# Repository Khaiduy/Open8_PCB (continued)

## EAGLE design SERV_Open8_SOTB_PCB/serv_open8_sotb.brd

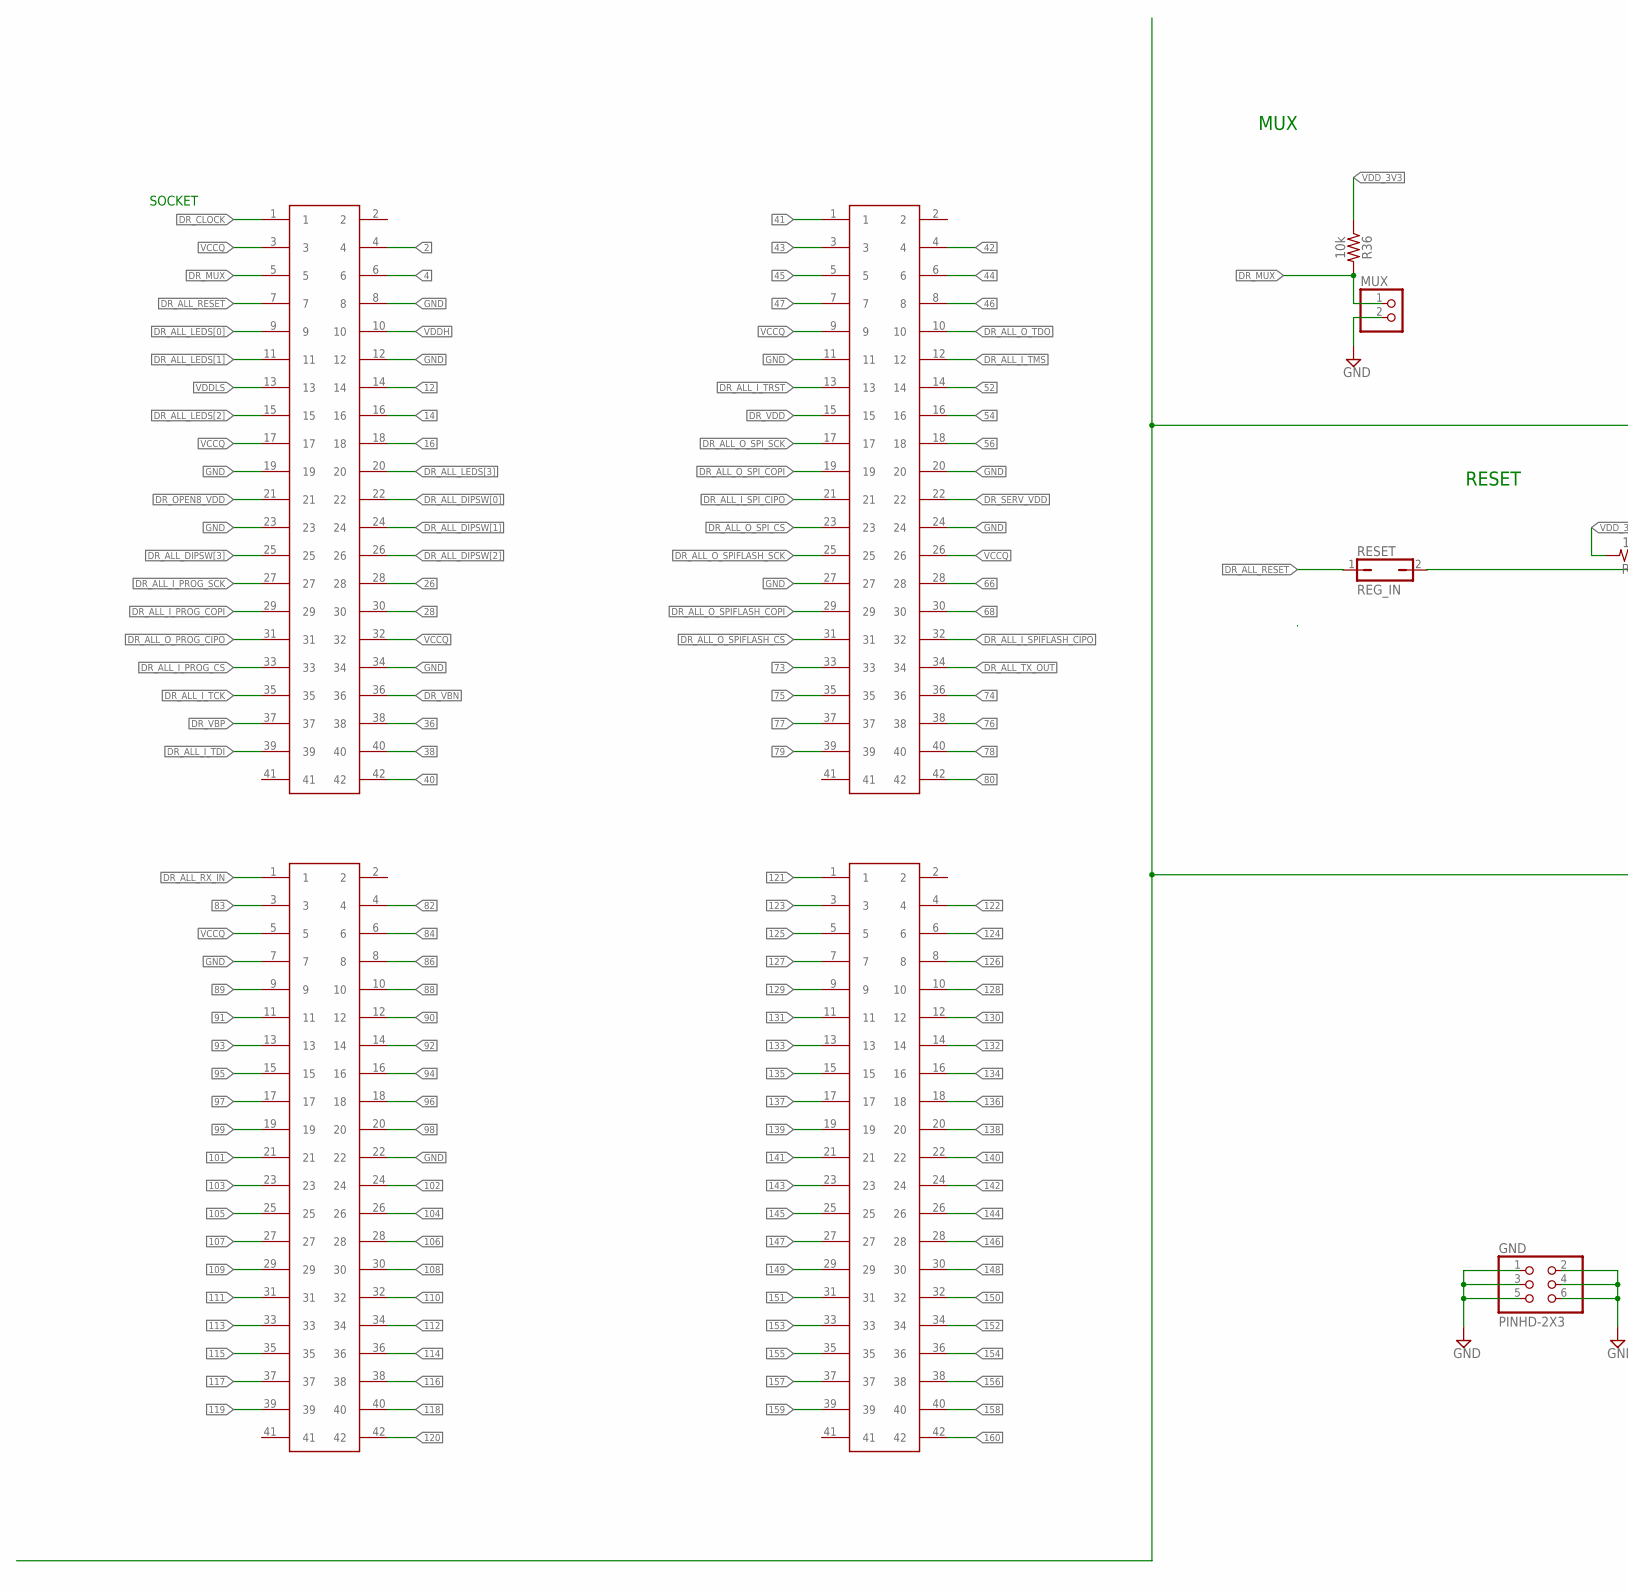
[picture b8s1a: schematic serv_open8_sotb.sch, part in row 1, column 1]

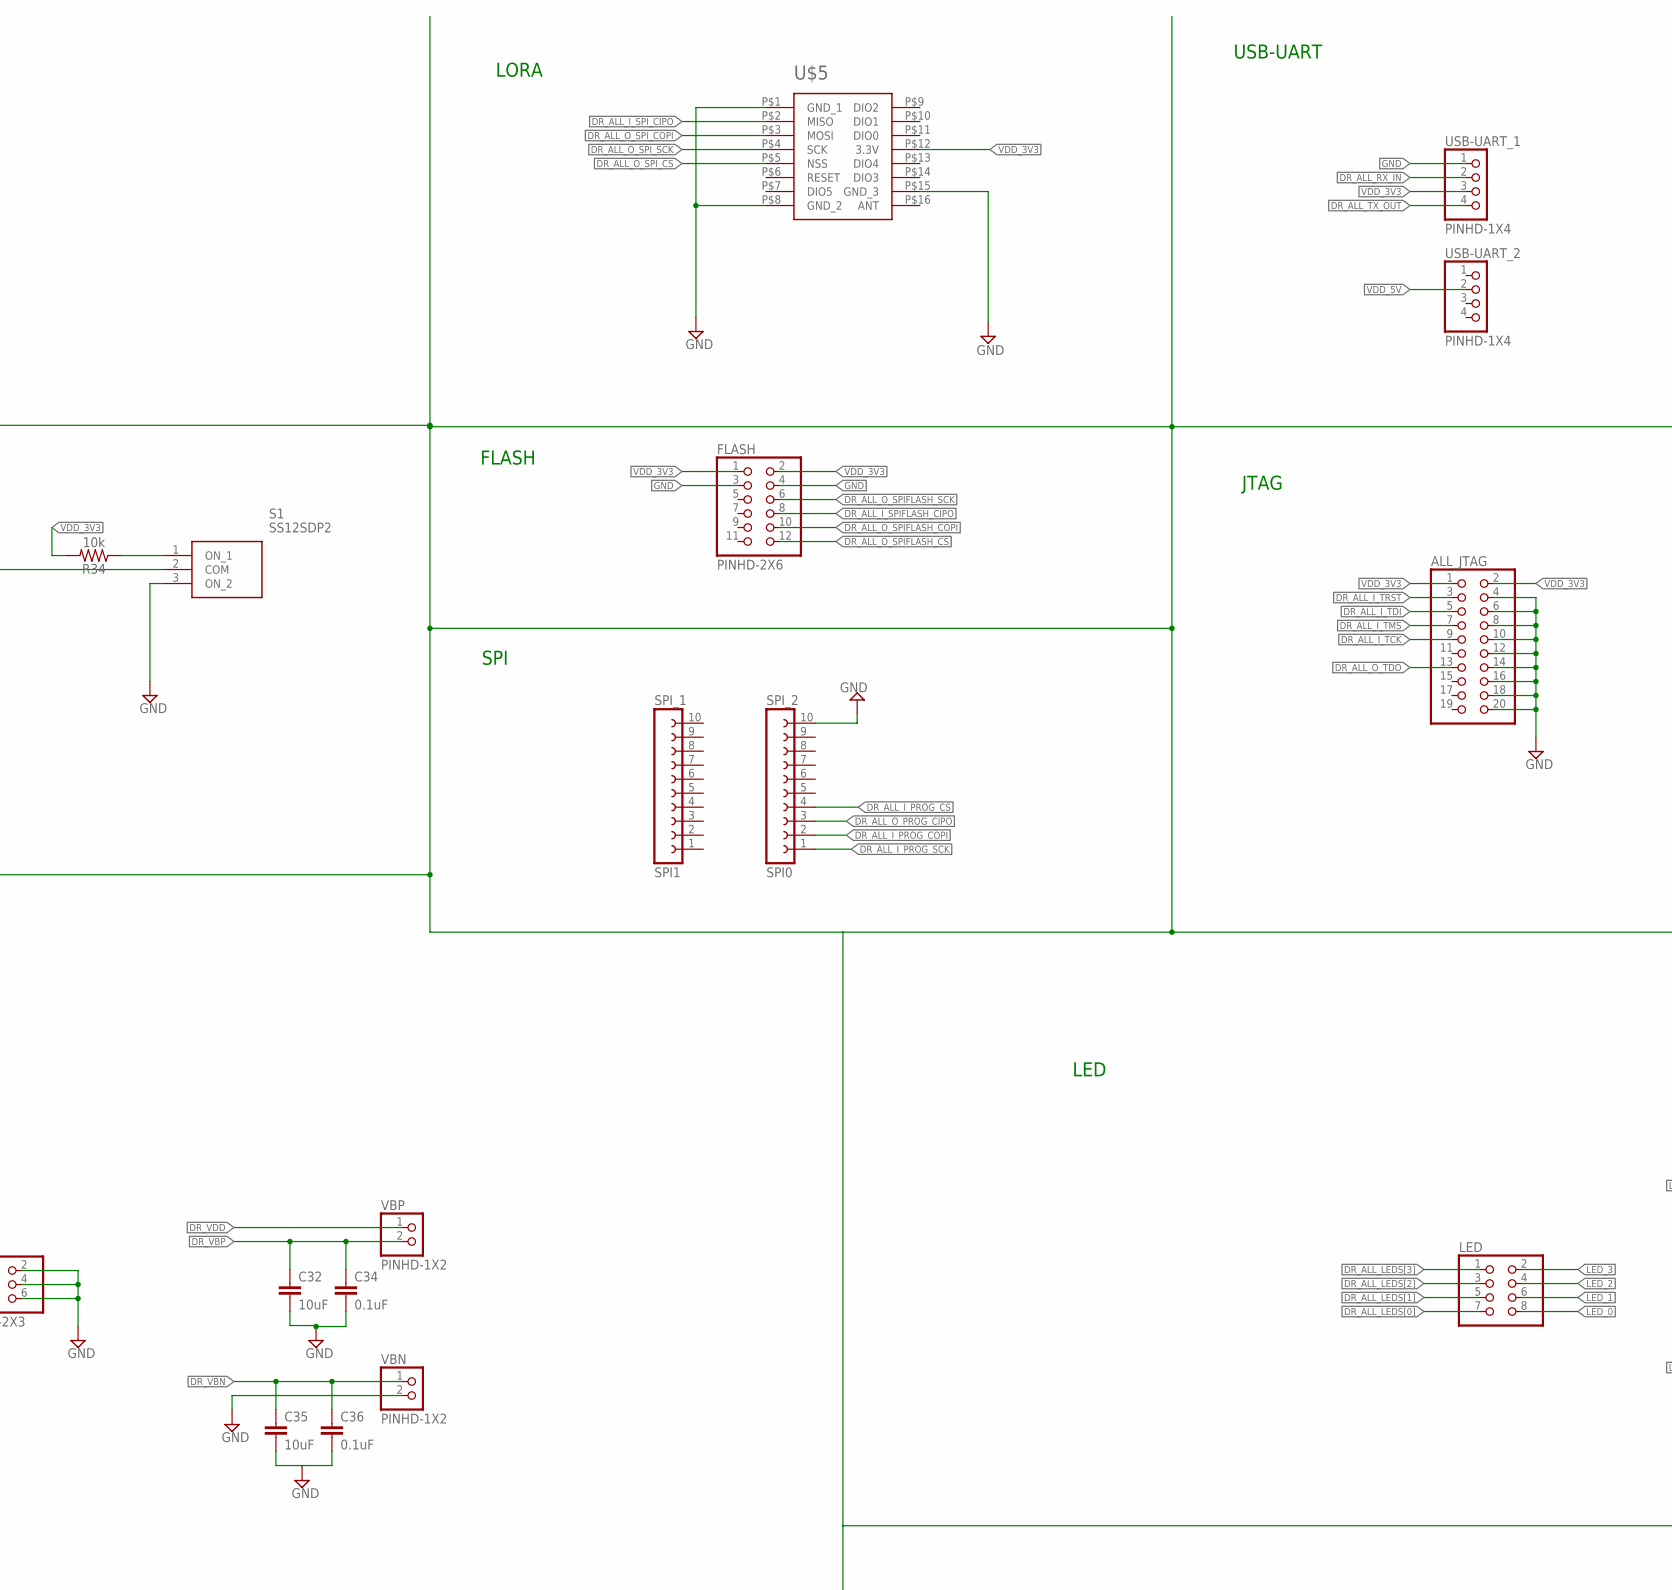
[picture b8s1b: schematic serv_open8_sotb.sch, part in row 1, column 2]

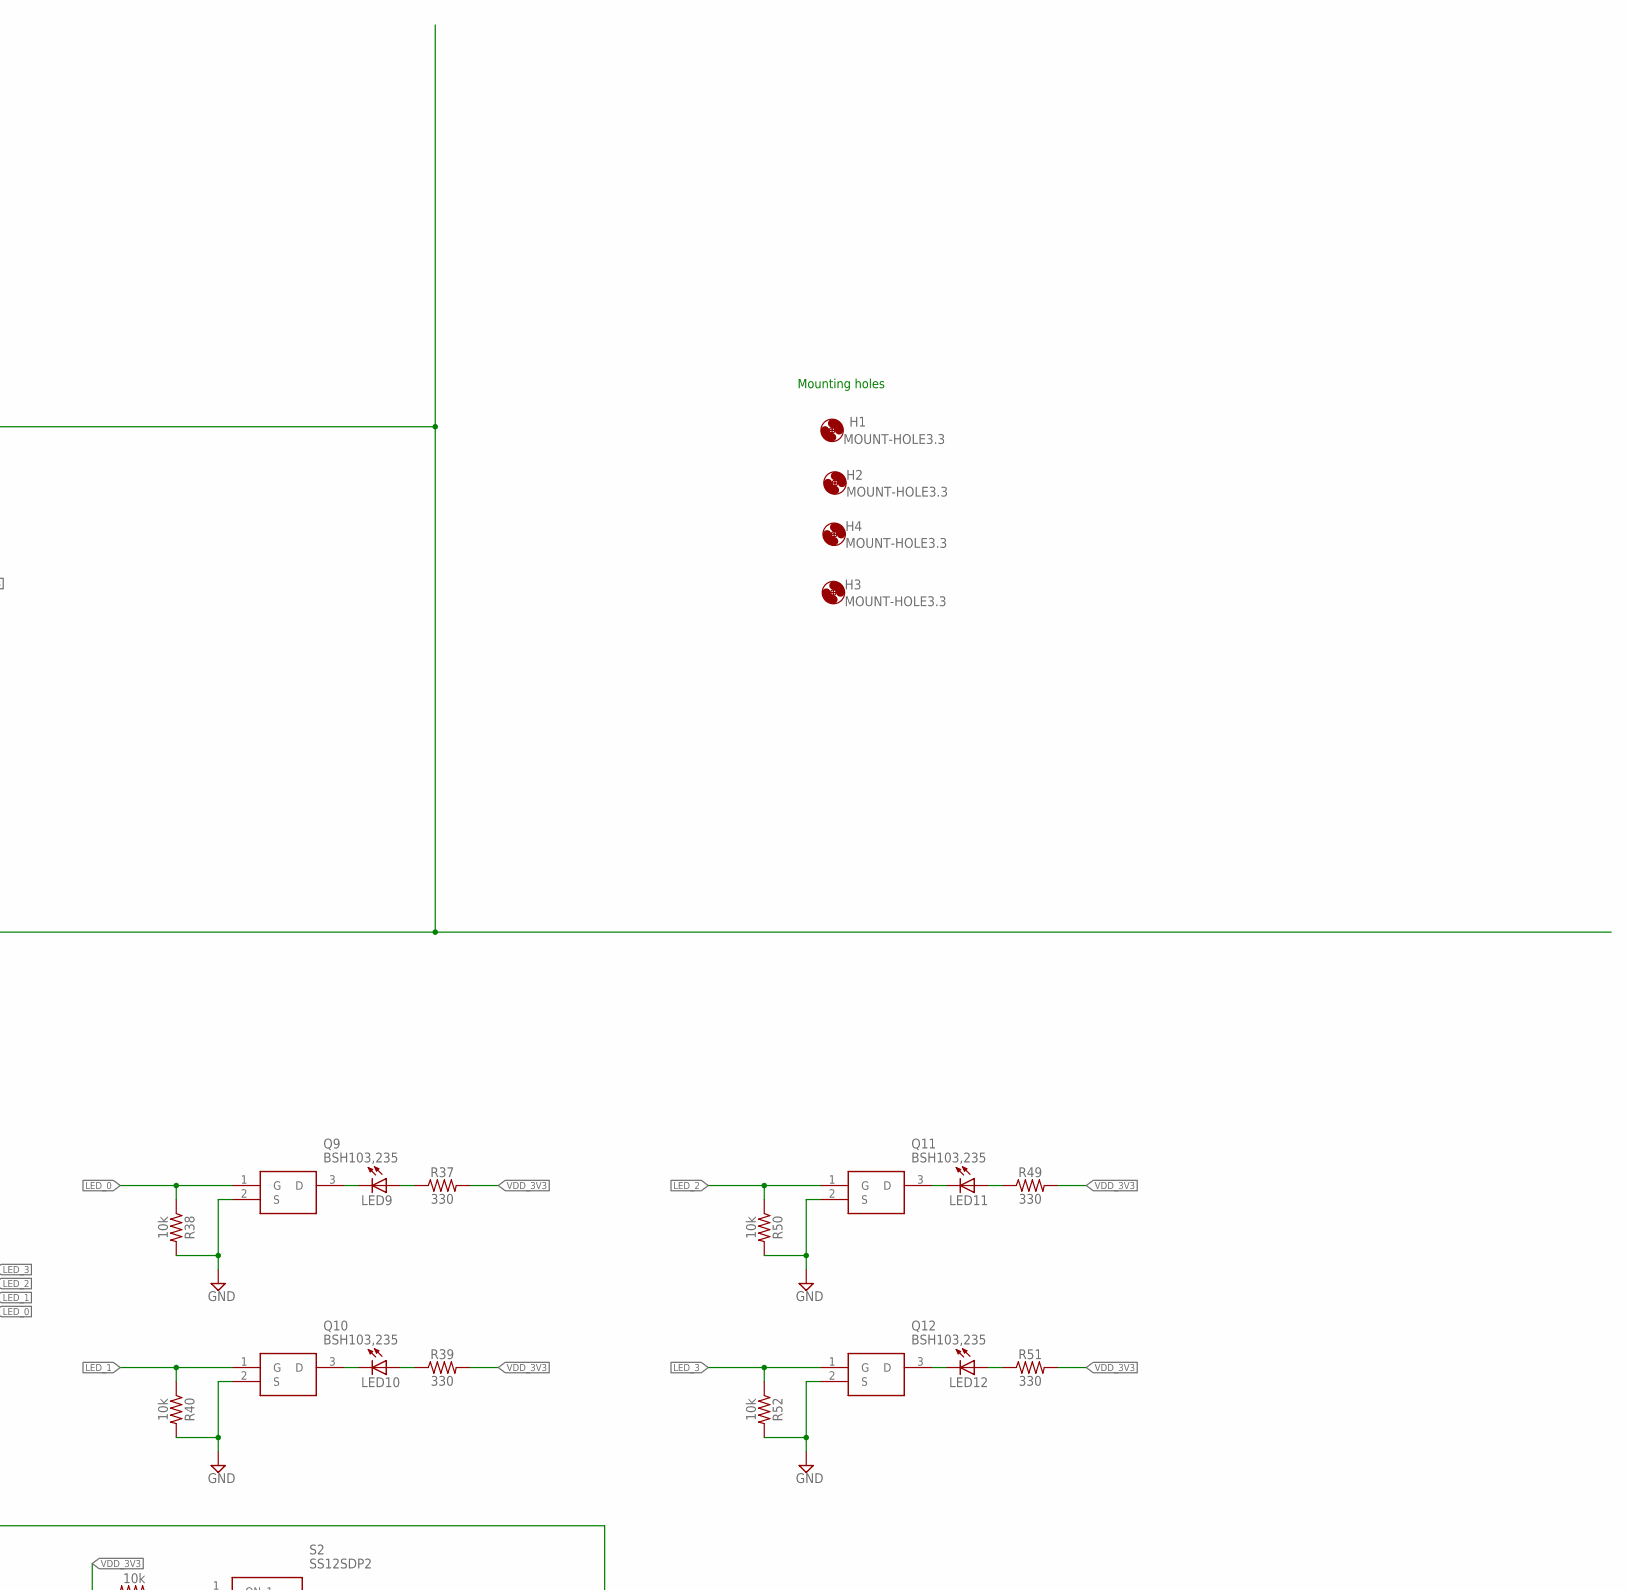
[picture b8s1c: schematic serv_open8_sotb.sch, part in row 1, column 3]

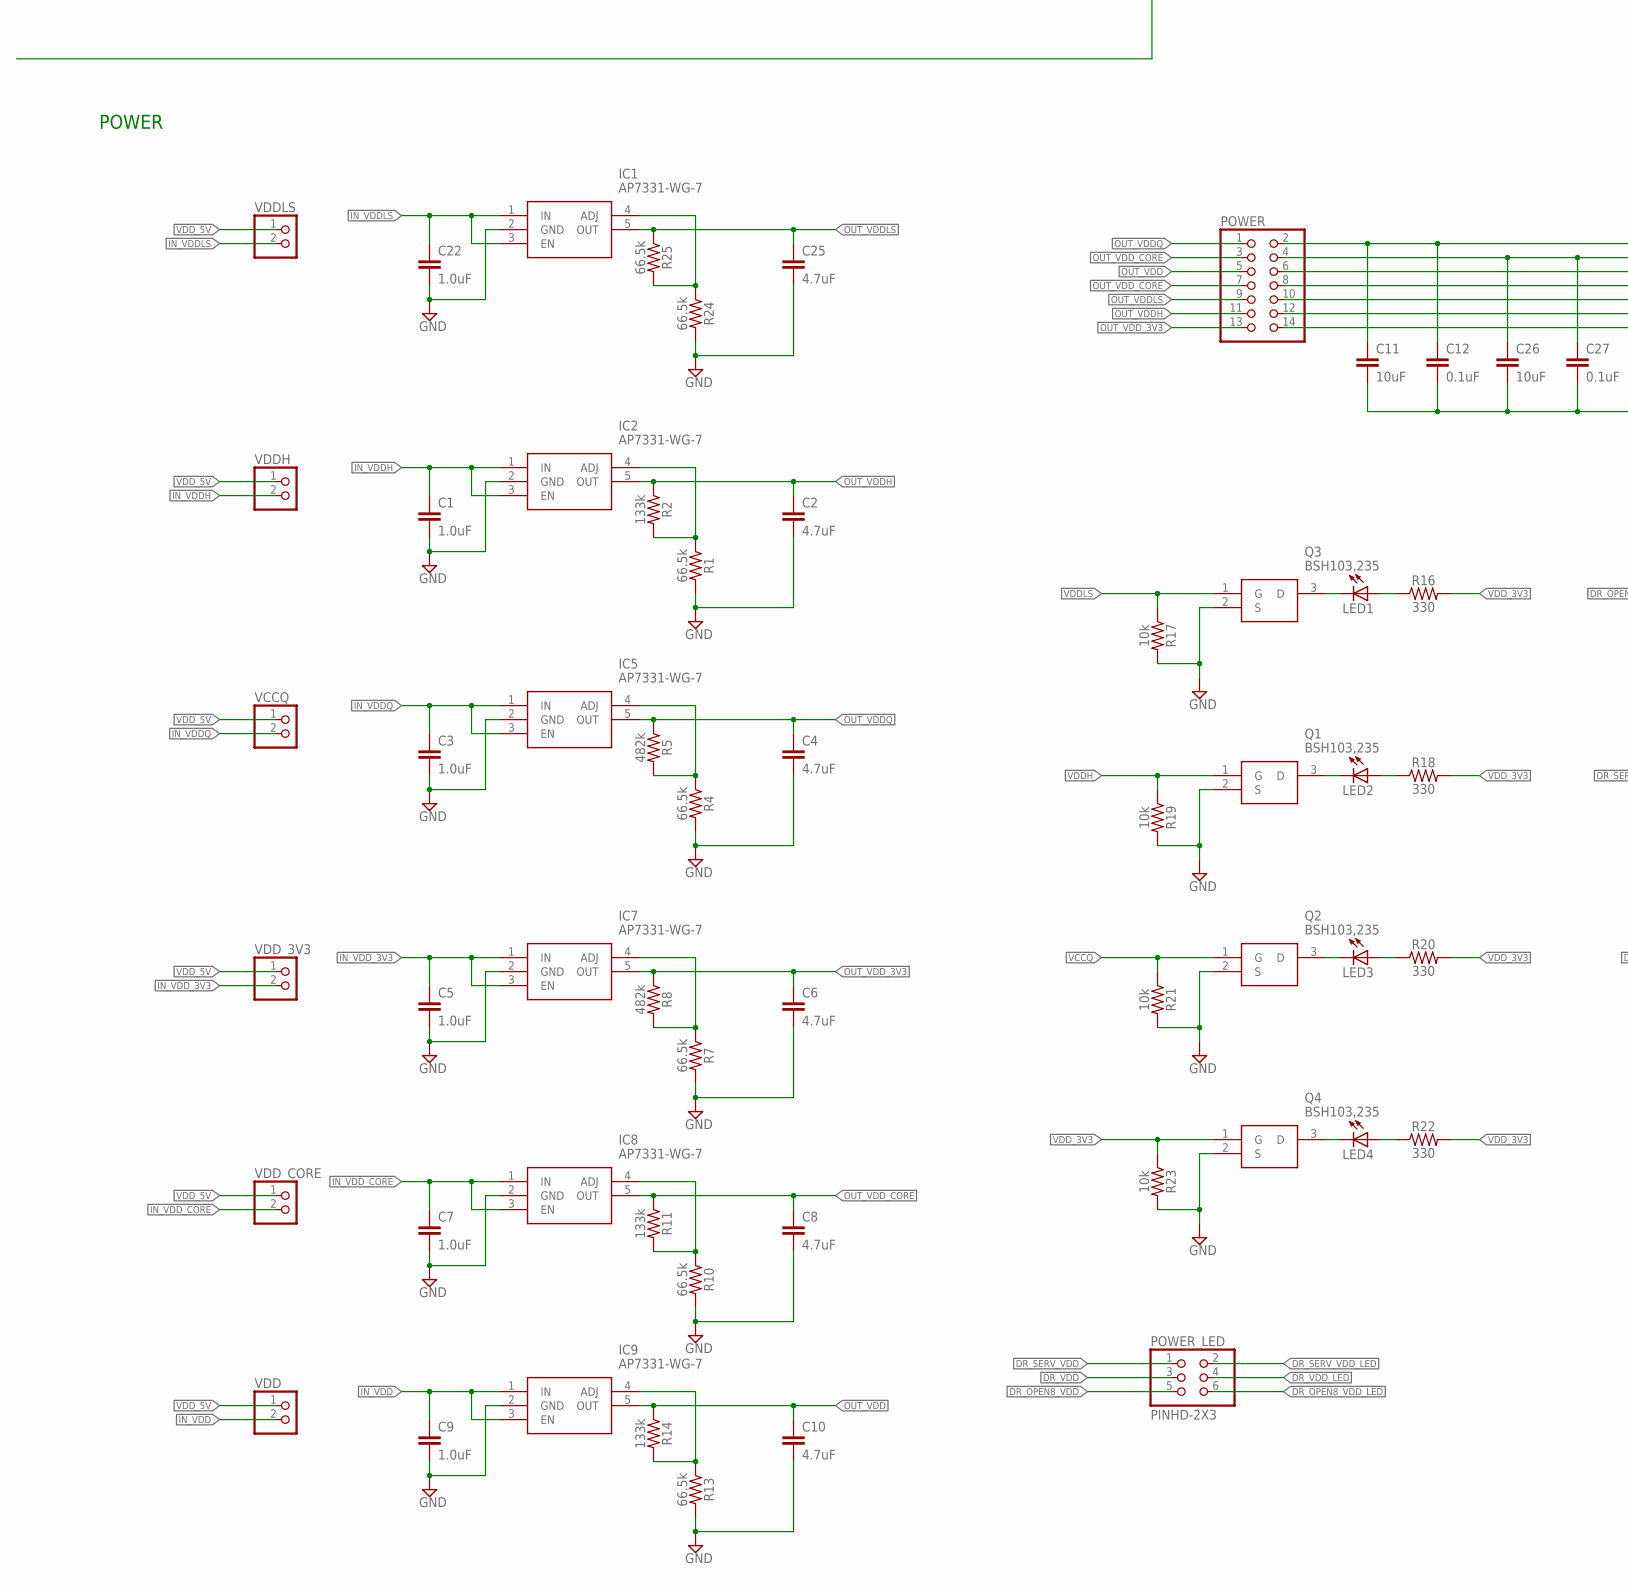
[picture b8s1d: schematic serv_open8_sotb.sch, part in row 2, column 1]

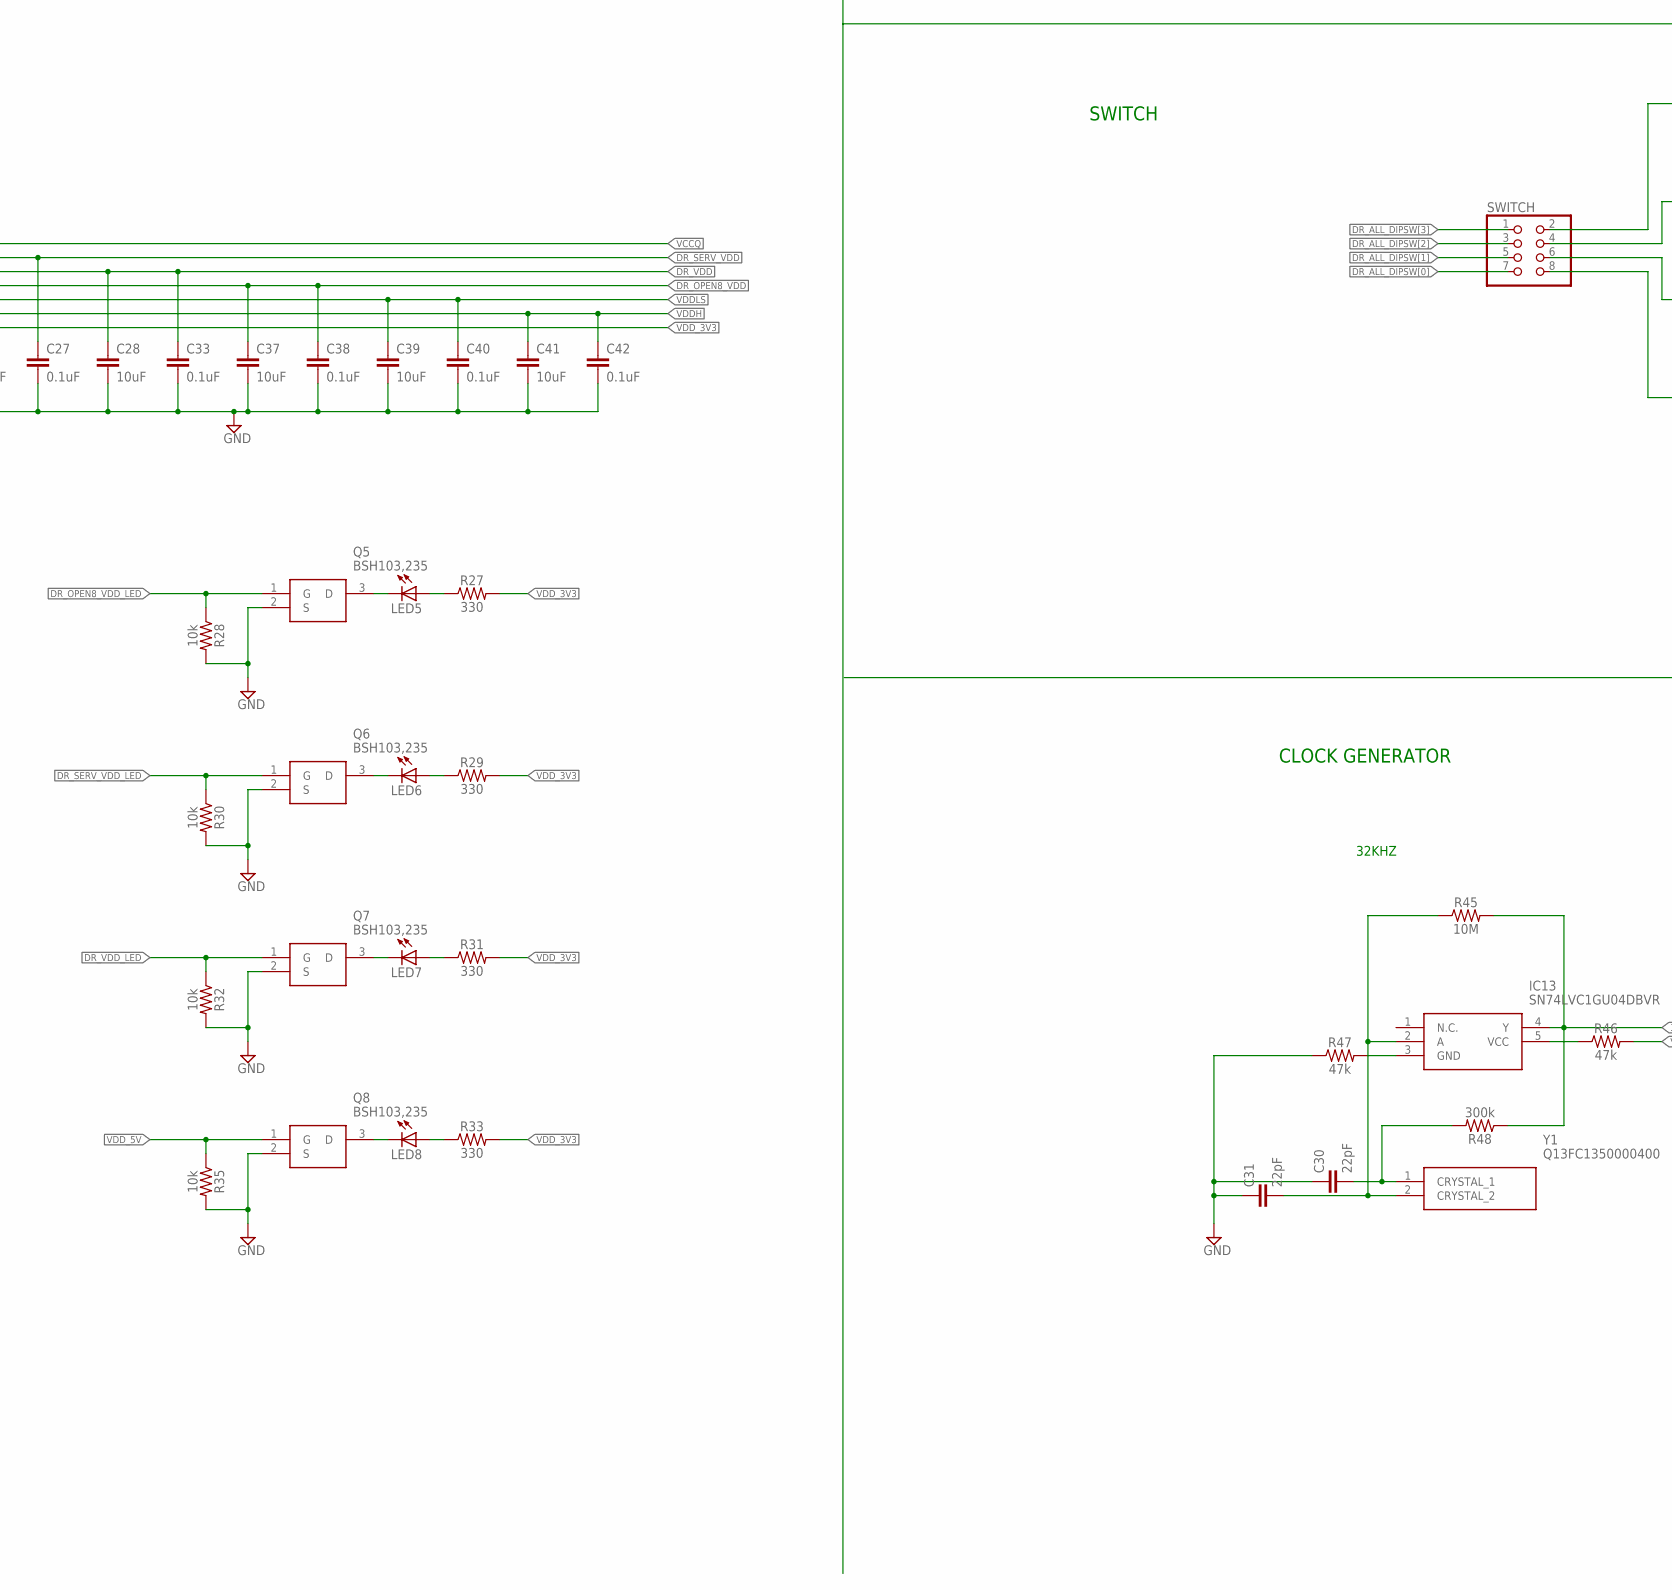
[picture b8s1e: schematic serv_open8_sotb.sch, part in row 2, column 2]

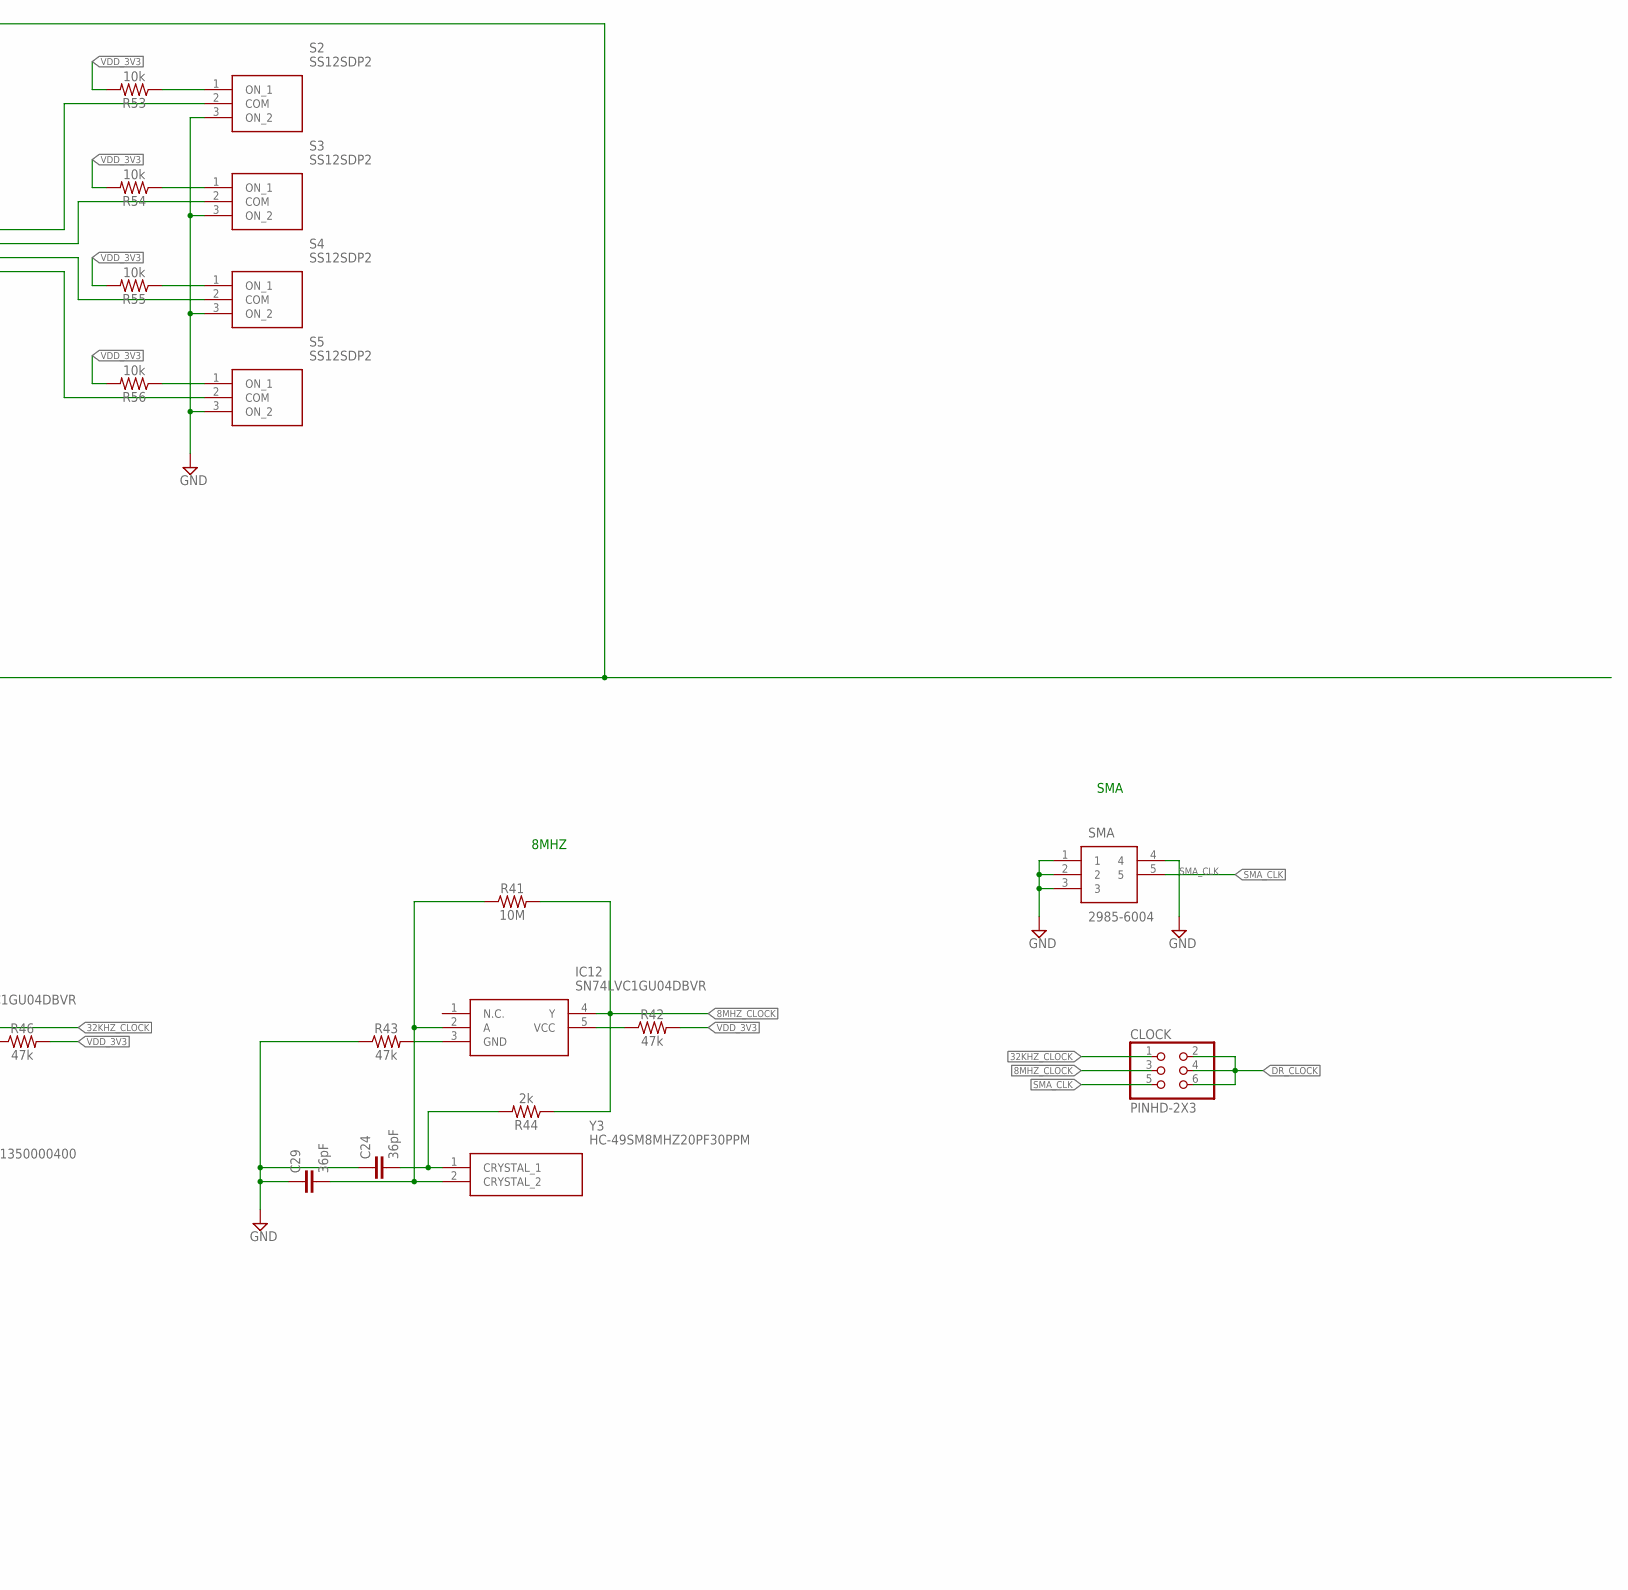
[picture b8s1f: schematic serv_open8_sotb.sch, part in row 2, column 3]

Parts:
ALL_JTAG: PINHD-2X10; 2X10
C1, C3, C5, C7, C9, C22: 1.0uF; 0805
C2, C4, C6, C8, C10, C25: 4.7uF; 0805
C11, C26, C28, C32, C35, C37, C39, C41: 10uF; 0805
C12, C27, C33, C34, C36, C38, C40, C42: 0.1uF; 0805
C24, C29: 36pF; 0805
C30, C31: 22pF; 0805
CLOCK: PINHD-2X3; 2X03
FLASH: PINHD-2X6; 2X06
GND: PINHD-2X3; 2X03
H1, H2, H3, H4: MOUNT-HOLE3.3; 3,3
IC1, IC2, IC5, IC7, IC8, IC9: AP7331-WG-7; SOT95P285X145-5N
IC12, IC13: SN74LVC1GU04DBVR; SOT95P280X145-5N
LED: PINHD-2X4; 2X04
LED1, LED2, LED3, LED4, LED5, LED6, LED7, LED8, LED9, LED10, LED11, LED12: LEDCHIP-LED0805; CHIP-LED0805
MUX: PINHD-1X2; 1X02
POWER: PINHD-2X7; 2X07
POWER_LED: PINHD-2X3; 2X03
Q1, Q2, Q3, Q4, Q5, Q6, Q7, Q8, Q9, Q10, Q11, Q12: BSH103,235; SOT95P230X110-3N
R1, R4, R7, R10, R13, R24, R25: 66.5k; 0805
R2, R11, R14: 133k; 0805
R5, R8: 482k; 0805
R16, R18, R20, R22, R27, R29, R31, R33, R37, R39, R49, R51: 330; 0805
R17, R19, R21, R23, R28, R30, R32, R34, R35, R36, R38, R40, R50, R52, R53, R54, R55, R56: 10k; 0805
R41, R45: 10M; 0805
R42, R43, R46, R47: 47k; 0805
R44: 2k; 0805
R48: 300k; 0805
RESET: REG_IN; JP1
S1, S2, S3, S4, S5: SS12SDP2
SMA: 2985-6004; 29856004
SPI_1: SPI1; FE10
SPI_2: SPI0; FE10
SWITCH: PINHD-2X4; 2X04
U$1, U$2, U$3, U$4: 2X41_HEADER
U$5: RFM95W-915S2
USB-UART_1, USB-UART_2: PINHD-1X4; 1X04
VBN: PINHD-1X2; 1X02
VBP: PINHD-1X2; 1X02
VCCQ: PINHD-1X2; 1X02
VDD: PINHD-1X2; 1X02
VDDH: PINHD-1X2; 1X02
VDDLS: PINHD-1X2; 1X02
VDD_3V3: PINHD-1X2; 1X02
VDD_CORE: PINHD-1X2; 1X02
Y1: Q13FC1350000400
Y3: HC-49SM8MHZ20PF30PPM; HC49SM8MHZ20PF30PPM

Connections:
2: U$1.4
4: U$1.6
8MHZ_CLOCK: CLOCK.3, IC12.4 (Y), R41.2, R44.1
12: U$1.14
14: U$1.16
16: U$1.18
26: U$1.28
28: U$1.30
32KHZ_CLOCK: CLOCK.1, IC13.4 (Y), R45.2, R48.1
36: U$1.38
38: U$1.40
40: U$1.42
41: U$2.1
42: U$2.4
43: U$2.3
44: U$2.6
45: U$2.5
46: U$2.8
47: U$2.7
52: U$2.14
54: U$2.16
56: U$2.18
66: U$2.28
68: U$2.30
73: U$2.33
74: U$2.36
75: U$2.35
76: U$2.38
77: U$2.37
78: U$2.40
79: U$2.39
80: U$2.42
82: U$3.4
83: U$3.3
84: U$3.6
86: U$3.8
88: U$3.10
89: U$3.9
90: U$3.12
91: U$3.11
92: U$3.14
93: U$3.13
94: U$3.16
95: U$3.15
96: U$3.18
97: U$3.17
98: U$3.20
99: U$3.19
101: U$3.21
102: U$3.24
103: U$3.23
104: U$3.26
105: U$3.25
106: U$3.28
107: U$3.27
108: U$3.30
109: U$3.29
110: U$3.32
111: U$3.31
112: U$3.34
113: U$3.33
114: U$3.36
115: U$3.35
116: U$3.38
117: U$3.37
118: U$3.40
119: U$3.39
120: U$3.42
121: U$4.1
122: U$4.4
123: U$4.3
124: U$4.6
125: U$4.5
126: U$4.8
127: U$4.7
128: U$4.10
129: U$4.9
130: U$4.12
131: U$4.11
132: U$4.14
133: U$4.13
134: U$4.16
135: U$4.15
136: U$4.18
137: U$4.17
138: U$4.20
139: U$4.19
140: U$4.22
141: U$4.21
142: U$4.24
143: U$4.23
144: U$4.26
145: U$4.25
146: U$4.28
147: U$4.27
148: U$4.30
149: U$4.29
150: U$4.32
151: U$4.31
152: U$4.34
153: U$4.33
154: U$4.36
155: U$4.35
156: U$4.38
157: U$4.37
158: U$4.40
159: U$4.39
160: U$4.42
DR_ALL_DIPSW[0]: SWITCH.7, U$1.22
DR_ALL_DIPSW[1]: SWITCH.5, U$1.24
DR_ALL_DIPSW[2]: SWITCH.3, U$1.26
DR_ALL_DIPSW[3]: SWITCH.1, U$1.25
DR_ALL_I_PROG_COPI: SPI_2.2, U$1.29
DR_ALL_I_PROG_CS: SPI_2.4, U$1.33
DR_ALL_I_PROG_SCK: SPI_2.1, U$1.27
DR_ALL_I_SPIFLASH_CIPO: FLASH.8, U$2.32
DR_ALL_I_SPI_CIPO: U$2.21, U$5.P$2 (MISO)
DR_ALL_I_TCK: ALL_JTAG.9, U$1.35
DR_ALL_I_TDI: ALL_JTAG.5, U$1.39
DR_ALL_I_TMS: ALL_JTAG.7, U$2.12
DR_ALL_I_TRST: ALL_JTAG.3, U$2.13
DR_ALL_LEDS[0]: LED.7, U$1.9
DR_ALL_LEDS[1]: LED.5, U$1.11
DR_ALL_LEDS[2]: LED.3, U$1.15
DR_ALL_LEDS[3]: LED.1, U$1.20
DR_ALL_O_PROG_CIPO: SPI_2.3, U$1.31
DR_ALL_O_SPIFLASH_COPI: FLASH.10, U$2.29
DR_ALL_O_SPIFLASH_CS: FLASH.12, U$2.31
DR_ALL_O_SPIFLASH_SCK: FLASH.6, U$2.25
DR_ALL_O_SPI_COPI: U$2.19, U$5.P$3 (MOSI)
DR_ALL_O_SPI_CS: U$2.23, U$5.P$5 (NSS)
DR_ALL_O_SPI_SCK: U$2.17, U$5.P$4 (SCK)
DR_ALL_O_TDO: ALL_JTAG.13, U$2.10
DR_ALL_RESET: RESET.1, U$1.7
DR_ALL_RX_IN: U$3.1, USB-UART_1.2
DR_ALL_TX_OUT: U$2.34, USB-UART_1.4
DR_CLOCK: CLOCK.2, CLOCK.4, CLOCK.6, U$1.1
DR_MUX: MUX.1, R36.2, U$1.5
DR_OPEN8_VDD: C37.1, C38.1, POWER.8, POWER_LED.5, U$1.21
DR_OPEN8_VDD_LED: POWER_LED.6, Q5.1 (G), R28.1
DR_SERV_VDD: C26.1, C27.1, POWER.4, POWER_LED.1, U$2.22
DR_SERV_VDD_LED: POWER_LED.2, Q6.1 (G), R30.1
DR_VBN: C35.1, C36.1, U$1.36, VBN.1
DR_VBP: C32.1, C34.1, U$1.37, VBP.2
DR_VDD: C28.1, C33.1, POWER.6, POWER_LED.3, U$2.15, VBP.1
DR_VDD_LED: POWER_LED.4, Q7.1 (G), R32.1
GND: ALL_JTAG.4, ALL_JTAG.6, ALL_JTAG.8, ALL_JTAG.10, ALL_JTAG.12, ALL_JTAG.14, ALL_JTAG.16, ALL_JTAG.18, ALL_JTAG.20, C1.2, C2.2, C3.2, C4.2, C5.2, C6.2, C7.2, C8.2, C9.2, C10.2, C11.2, C12.2, C22.2, C24.1, C25.2, C26.2, C27.2, C28.2, C29.1, C30.1, C31.1, C32.2, C33.2, C34.2, C35.2, C36.2, C37.2, C38.2, C39.2, C40.2, C41.2, C42.2, FLASH.3, FLASH.4, GND.1, GND.2, GND.3, GND.4, GND.5, GND.6, IC1.2 (GND), IC2.2 (GND), IC5.2 (GND), IC7.2 (GND), IC8.2 (GND), IC9.2 (GND), MUX.2, Q1.2 (S), Q2.2 (S), Q3.2 (S), Q4.2 (S), Q5.2 (S), Q6.2 (S), Q7.2 (S), Q8.2 (S), Q9.2 (S), Q10.2 (S), Q11.2 (S), Q12.2 (S), R1.2, R4.2, R7.2, R10.2, R13.2, R17.2, R19.2, R21.2, R23.2, R24.2, R28.2, R30.2, R32.2, R35.2, R38.2, R40.2, R43.1, R47.1, R50.2, R52.2, S1.3 (ON_2), S2.3 (ON_2), S3.3 (ON_2), S4.3 (ON_2), S5.3 (ON_2), SMA.1, SMA.2, SMA.3, SMA.4, SPI_2.10, U$1.8, U$1.12, U$1.19, U$1.23, U$1.34, U$2.11, U$2.20, U$2.24, U$2.27, U$3.7, U$3.22, U$5.P$1 (GND_1), U$5.P$8 (GND_2), U$5.P$15 (GND_3), USB-UART_1.1, VBN.2
IN_VDD: C9.1, IC9.1 (IN), IC9.3 (EN), VDD.2
IN_VDDH: C1.1, IC2.1 (IN), IC2.3 (EN), VDDH.2
IN_VDDLS: C22.1, IC1.1 (IN), IC1.3 (EN), VDDLS.2
IN_VDDQ: C3.1, IC5.1 (IN), IC5.3 (EN), VCCQ.2
IN_VDD_3V3: C5.1, IC7.1 (IN), IC7.3 (EN), VDD_3V3.2
IN_VDD_CORE: C7.1, IC8.1 (IN), IC8.3 (EN), VDD_CORE.2
LED_0: LED.8, Q9.1 (G), R38.1
LED_1: LED.6, Q10.1 (G), R40.1
LED_2: LED.4, Q11.1 (G), R50.1
LED_3: LED.2, Q12.1 (G), R52.1
unnamed: IC2.4 (ADJ), R1.1, R2.2
unnamed: IC5.4 (ADJ), R4.1, R5.2
unnamed: IC7.4 (ADJ), R7.1, R8.2
unnamed: IC8.4 (ADJ), R10.1, R11.2
unnamed: IC9.4 (ADJ), R13.1, R14.2
unnamed: R34.1, S1.1 (ON_1)
unnamed: LED2.C, Q1.3 (D)
unnamed: LED1.C, Q3.3 (D)
unnamed: LED2.A, R18.1
unnamed: LED9.C, Q9.3 (D)
unnamed: LED9.A, R37.1
unnamed: LED1.A, R16.1
unnamed: IC1.4 (ADJ), R24.1, R25.2
unnamed: LED3.C, Q2.3 (D)
unnamed: LED3.A, R20.1
unnamed: RESET.2, S1.2 (COM)
unnamed: LED4.C, Q4.3 (D)
unnamed: LED4.A, R22.1
unnamed: LED10.C, Q10.3 (D)
unnamed: LED5.C, Q5.3 (D)
unnamed: LED5.A, R27.1
unnamed: LED10.A, R39.1
unnamed: LED6.C, Q6.3 (D)
unnamed: LED6.A, R29.1
unnamed: C29.2, IC12.2 (A), R41.1, Y3.2 (CRYSTAL_2)
unnamed: LED7.C, Q7.3 (D)
unnamed: LED7.A, R31.1
unnamed: C24.2, R44.2, Y3.1 (CRYSTAL_1)
unnamed: LED8.C, Q8.3 (D)
unnamed: LED8.A, R33.1
unnamed: IC12.3 (GND), R43.2
unnamed: IC12.5 (VCC), R42.1
unnamed: C31.2, IC13.2 (A), R45.1, Y1.2 (CRYSTAL_2)
unnamed: LED11.C, Q11.3 (D)
unnamed: C30.2, R48.2, Y1.1 (CRYSTAL_1)
unnamed: LED11.A, R49.1
unnamed: IC13.3 (GND), R47.2
unnamed: LED12.C, Q12.3 (D)
unnamed: LED12.A, R51.1
unnamed: IC13.5 (VCC), R46.1
unnamed: R53.1, S2.1 (ON_1)
unnamed: R54.1, S3.1 (ON_1)
unnamed: R55.1, S4.1 (ON_1)
unnamed: R56.1, S5.1 (ON_1)
unnamed: S2.2 (COM), SWITCH.2
unnamed: S3.2 (COM), SWITCH.4
unnamed: S4.2 (COM), SWITCH.6
unnamed: S5.2 (COM), SWITCH.8
OUT_VDD: C10.1, IC9.5 (OUT), POWER.5, R14.1
OUT_VDDH: C2.1, IC2.5 (OUT), POWER.11, R2.1
OUT_VDDLS: C25.1, IC1.5 (OUT), POWER.9, R25.1
OUT_VDDQ: C4.1, IC5.5 (OUT), POWER.1, R5.1
OUT_VDD_3V3: C6.1, IC7.5 (OUT), POWER.13, R8.1
OUT_VDD_CORE: C8.1, IC8.5 (OUT), POWER.3, POWER.7, R11.1
SMA_CLK: CLOCK.5, SMA.5
VCCQ: C11.1, C12.1, POWER.2, Q2.1 (G), R21.1, U$1.3, U$1.17, U$1.32, U$2.9, U$2.26, U$3.5
VDDH: C41.1, C42.1, POWER.12, Q1.1 (G), R19.1, U$1.10
VDDLS: C39.1, C40.1, POWER.10, Q3.1 (G), R17.1, U$1.13
VDD_3V3: ALL_JTAG.1, ALL_JTAG.2, FLASH.1, FLASH.2, POWER.14, Q4.1 (G), R16.2, R18.2, R20.2, R22.2, R23.1, R27.2, R29.2, R31.2, R33.2, R34.2, R36.1, R37.2, R39.2, R42.2, R46.2, R49.2, R51.2, R53.2, R54.2, R55.2, R56.2, U$5.P$12 (3.3V), USB-UART_1.3
VDD_5V: Q8.1 (G), R35.1, USB-UART_2.2, VCCQ.1, VDD.1, VDDH.1, VDDLS.1, VDD_3V3.1, VDD_CORE.1

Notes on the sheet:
SOCKET
RESET
CLOCK GENERATOR
32KHZ
8MHZ
SMA
Mounting holes
MUX
LORA
FLASH
SPI
USB-UART
JTAG
LED
SWITCH
POWER

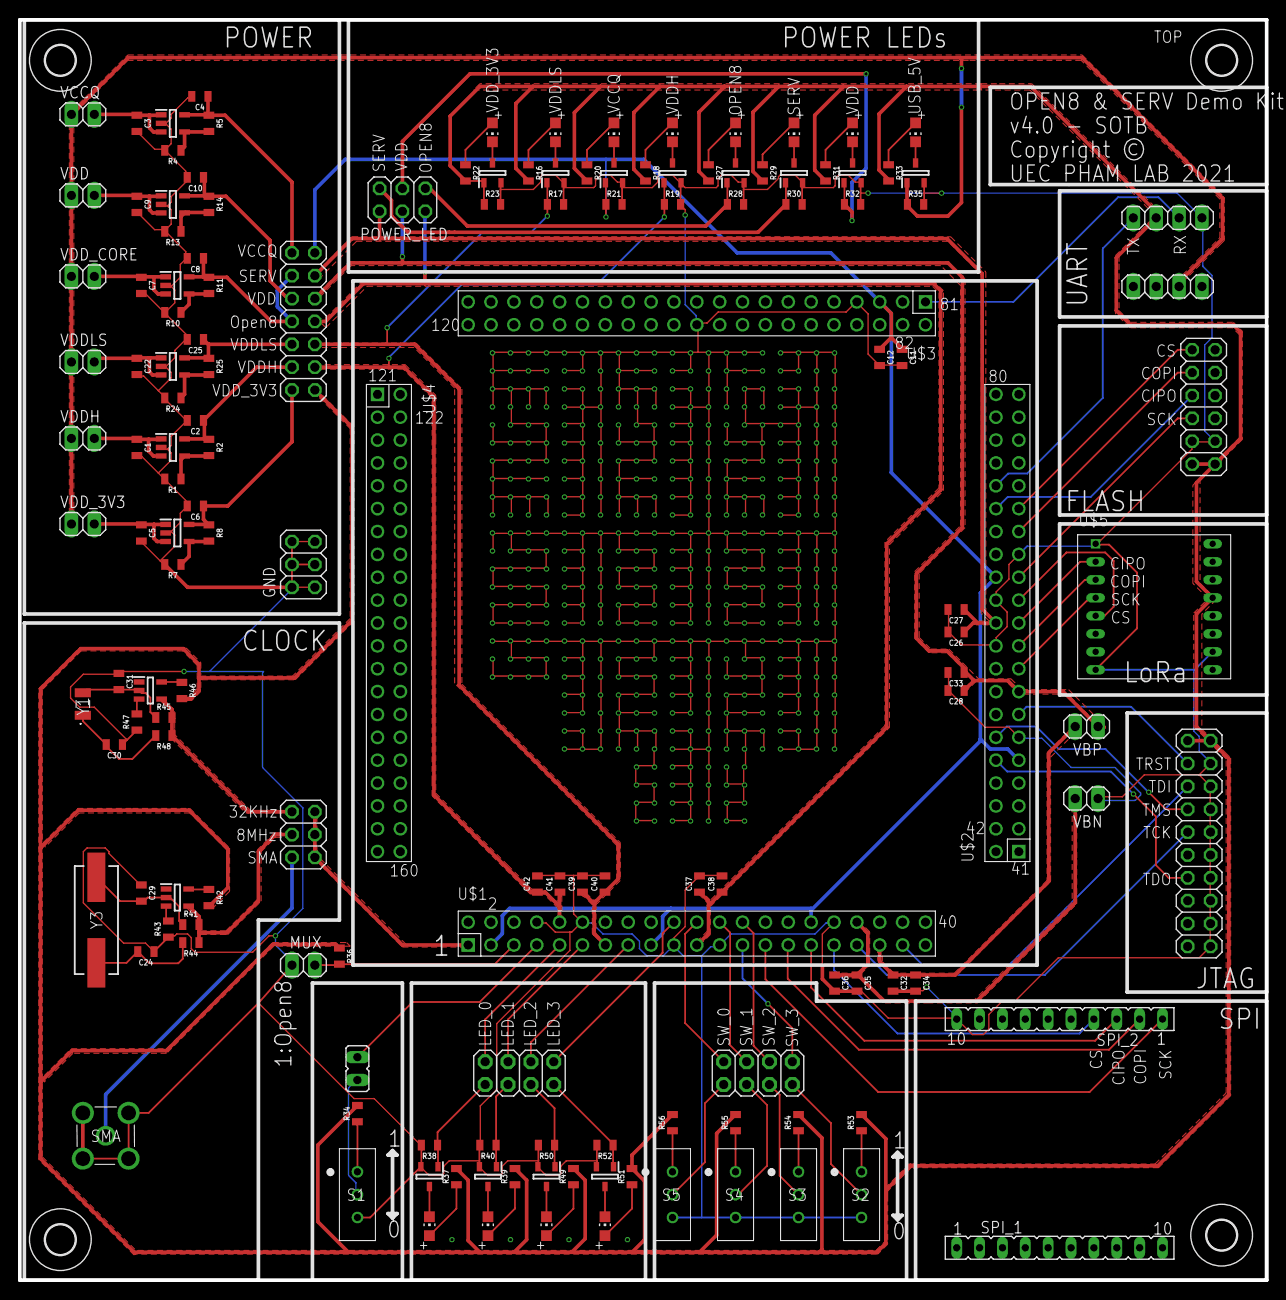
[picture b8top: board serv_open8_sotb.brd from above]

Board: 2 copper layers, 138.5 x 140.0 mm, 153 parts (0 on the bottom side), 111 nets.

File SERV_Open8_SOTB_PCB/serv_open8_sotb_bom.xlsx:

Comment | Designator | Footprint | LCSC Part #（optional）
LED | LED1, LED2, LED3, LED4, LED5, LED6, LED7, LED8, LED9, LED10, LED11, LED12 | 805 | C2290
0.1uF | C12, C27, C33, C34, C36, C38, C40, C42 | 805 | C476766
1.0uF | C1, C3, C5, C7, C9, C22 | 805 | C24123
10M | R41, R45 | 805 | C26108
10k | R17, R19, R21, R23, R28, R30, R32, R34, R35, R36, R38, R40, R50, R52, R53, R54,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 | 805 | C115309
10uF | C11, C26, C28, C32, C35, C37, C39, C41 | 805 | C15850
133k | R2, R11, R14 | 805 | C17452
22pF | C30, C31 | 805 | C1804
2k | R44 | 805 | C17604
300k | R48 | 805 | C17616
330 | R16, R18, R20, R22, R27, R29, R31, R33, R37, R39, R49, R51 | 805 | C17630
36pF | C24, C29 | 805 | C327231
4.7uF | C2, C4, C6, C8, C10, C25 | 805 | C1779
47k | R42, R43, R46, R47 | 805 | C17713
482k | R5, R8 | 805 | C17717
66.5k | R1, R4, R7, R10, R13, R24, R25 | 805 | C17791
AP7331-WG-7 | IC1, IC2, IC5, IC7, IC8, IC9 | SOT-25 | C212322
BSH103,235 | Q1, Q2, Q3, Q4, Q5, Q6, Q7, Q8, Q9, Q10, Q11, Q12 | SOT-23-3 | C88711
HC-49SM8MHZ20PF30PPM | Y3 | SMD-CRY-3.8x13.5_2P | C107426
SN74LVC1GU04DBVR | IC12, IC13 | SOT-23-5 | C81934
Q13FC1350000400 | Y1 | SMD-3215_2P | C32346
